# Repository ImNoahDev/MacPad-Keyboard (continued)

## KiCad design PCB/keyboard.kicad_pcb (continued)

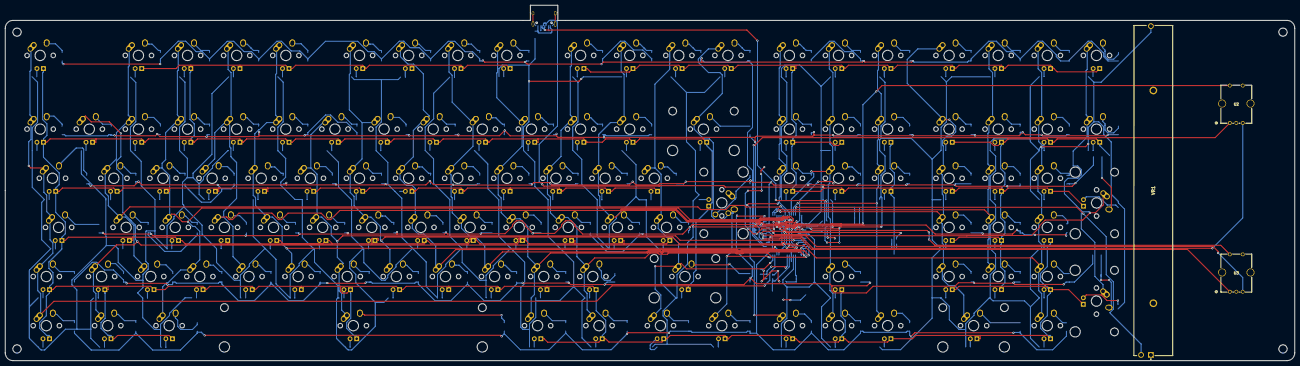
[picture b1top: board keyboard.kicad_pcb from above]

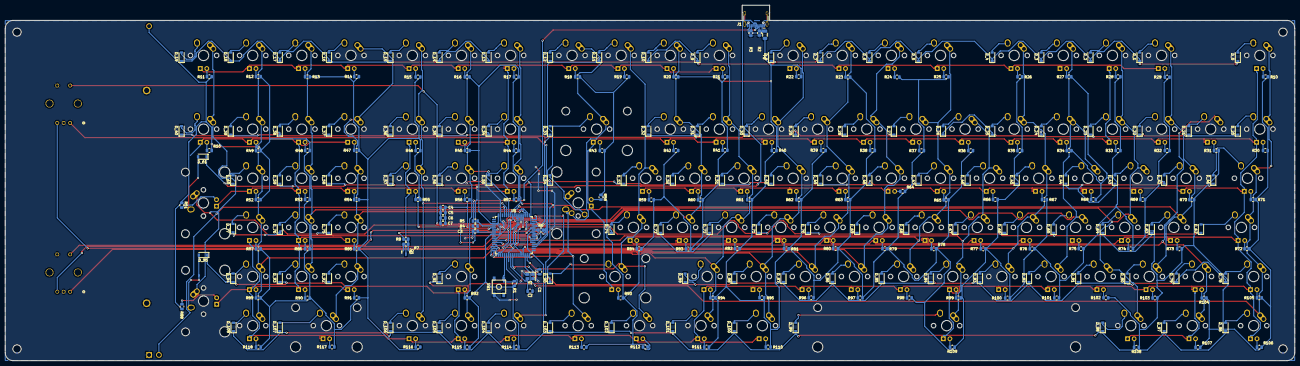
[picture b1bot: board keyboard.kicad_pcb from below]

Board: 2 copper layers, 500.0 x 137.8 mm, 351 parts (239 on the bottom side), 270 nets.

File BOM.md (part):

## PCB component breakdown

| Designator                                                                                           | Quantity | Value                       | Footprint                               | Package | MPN                | DNP | Mount_Type | Description                                                                            | Price    | Total    | URL                                                                       |
| ---------------------------------------------------------------------------------------------------- | -------- | --------------------------- | --------------------------------------- | ------- | ------------------ | --- | ---------- | -------------------------------------------------------------------------------------- | -------- | -------- | ------------------------------------------------------------------------- |
| C1, C2                                                                                               | 2        | 22pF                        | C_0805_2012Metric                       |         |                    |     | smt        |                                                                                        | $0.0011  | $0.0022  | https://jlcpcb.com/partdetail/1907-0402CG220J500NT/C1555                  |
| C3                                                                                                   | 1        | 1uF                         | C_0805_2012Metric                       |         |                    |     | smt        |                                                                                        | $0.0032  | $0.0064  | https://jlcpcb.com/partdetail/1944-CL10A105KO8NNNC/C1592                  |
| C4, C5, C6                                                                                           | 3        | 0.1uF                       | C_0805_2012Metric                       |         |                    |     | smt        |                                                                                        | $0.0011  | $0.0033  | https://jlcpcb.com/partdetail/1877-CL05B104KO5NNNC/C1525                  |
| C7                                                                                                   | 1        | 10uF                        | C_0805_2012Metric                       |         |                    |     | smt        |                                                                                        | $0.0028  | $0.0028  | https://jlcpcb.com/partdetail/2043-CL10A106MQ8NNNC/C1691                  |
| D_0, D_1, D_10, D_100, D_101, D_102, D_103, D_104, D_105, D_106, D_107, D_108, D_11, D_12, D_13, D_14, D_15, D_16, D_17, D_18, D_19, D_2, D_20, D_21, D_22, D_23, D_24, D_25, D_26, D_27, D_28, D_29, D_3, D_30, D_31, D_32, D_33, D_34, D_35, D_36, D_37, D_38, D_39, D_4, D_40, D_41, D_42, D_43, D_44, D_45, D_46, D_47, D_48, D_49, D_5, D_50, D_51, D_52, D_53, D_54, D_55, D_56, D_57, D_58, D_59, D_6, D_60, D_61, D_62, D_63, D_64, D_65, D_66, D_67, D_68, D_69, D_7, D_70, D_71, D_72, D_73, D_74, D_75, D_76, D_77, D_78, D_79, D_8, D_80, D_81, D_82, D_83, D_84, D_85, D_86, D_87, D_88, D_89, D_9, D_90, D_91, D_92, D_93, D_94, D_95, D_96, D_97, D_98, D_99 | 109      | D                           | D_SOD-123                               |         |                    |     | smt        |                                                                                        | $0.0052  | $0.57    | https://jlcpcb.com/partdetail/Shunye-ES1D_SOD_123FL/C7370889              |
| F1                                                                                                   | 1        | 500mA                       | Fuse_1206_3216Metric                    |         |                    |     | smt        |                                                                                        | $0.0365  | $0.0365  | https://jlcpcb.com/partdetail/JlcpcbAssembly-FUSE/C9900021114             |
| J1                                                                                                   | 1        | USB_C_Receptacle_USB2.0_14P | USB_C_Receptacle_HCTL_HC-TYPE-C-16P-01A |         |                    |     | smt        | USB 2.0-only 14P Type-C Receptacle connector                                           | $0.0365  | $0.0365  | https://jlcpcb.com/partdetail/JlcpcbAssembly-14P/C9900117666              |
| Q1                                                                                                   | 1        | AO3400A                     | SOT-23                                  |         |                    |     | smt        | 30V Vds, 5.7A Id, N-Channel MOSFET, SOT-23                                             | $0.0428  | $0.0428  | https://jlcpcb.com/partdetail/Alpha_OmegaSemicon-AO3400A/C20917           |
| R1, R6, R7                                                                                           | 3        | 10k                         | R_0805_2012Metric                       |         |                    |     | smt        | Resistor                                                                               | $0.0013  | $0.0039  | https://jlcpcb.com/partdetail/1841-1206W4J0103T5E/C1489                   |
| R10, R100, R101, R102, R103, R104, R105, R106, R107, R108, R109, R11, R110, R111, R112, R113, R114, R115, R116, R117, R118, R12, R13, R14, R15, R16, R17, R18, R19, R20, R21, R22, R23, R24, R25, R26, R27, R28, R29, R30, R31, R32, R33, R34, R35, R36, R37, R38, R39, R40, R41, R42, R43, R44, R45, R46, R47, R48, R49, R50, R51, R52, R53, R54, R55, R56, R57, R58, R59, R60, R61, R62, R63, R64, R65, R66, R67, R68, R69, R70, R71, R72, R73, R74, R75, R76, R77, R78, R79, R80, R81, R82, R83, R84, R85, R86, R87, R88, R89, R90, R91, R92, R93, R94, R95, R96, R97, R98, R99 | 109      | 120                         | R_0805_2012Metric                       |         |                    |     | smt        | Resistor                                                                               | $0.0008  | $0.0872  | https://jlcpcb.com/partdetail/23514-0603WAF1200T5E/C22787                 |
| R2, R3                                                                                               | 2        | 5.1k                        | R_0805_2012Metric                       |         |                    |     | smt        |                                                                                        | $0.0007  | $0.0014  | https://jlcpcb.com/partdetail/Yageo-RC0603JR075K1L/C14677                 |
| R4, R5                                                                                               | 2        | 22                          | R_0805_2012Metric                       |         |                    |     | smt        |                                                                                        | $0.0005  | $0.001   | https://jlcpcb.com/partdetail/1555-0603WAJ0220T5E/C1203                   |
| R8                                                                                                   | 1        | 220                         | R_0805_2012Metric                       |         |                    |     | smt        | Resistor                                                                               | $0.0004  | $0.0004  | https://jlcpcb.com/partdetail/1463-RC02W221JT/C1111                       |
| SW1                                                                                                  | 1        | SW_Push                     | SKQG-1155865                            |         |                    |     | smt        |                                                                                        | $0.2385  | $0.2385  | https://jlcpcb.com/partdetail/Panasonic-EVQQ2B03W/C79178                  |
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
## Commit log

2025-05-22 Init
2025-05-22 Microcontroller + layout
2025-05-22 Layout + wiring
2025-05-23 Layout + routing
2025-05-23 Plate
2025-05-23 Case
2025-05-24 Add screw holes to case
2025-05-24 Update BOM
2025-05-26 Fix PCB
2025-05-26 Firmware
2025-05-28 add render
2025-05-28 images
2025-05-28 images2
2025-05-29 New controller
2025-05-29 Update PCB
2025-05-29 Case upgrades
2025-05-29 Spelling
2025-05-30 Image
2025-05-30 image repair
2025-05-30 Render
2025-05-31 Fix image
2025-05-31 3d model
2025-06-02 repo.png
